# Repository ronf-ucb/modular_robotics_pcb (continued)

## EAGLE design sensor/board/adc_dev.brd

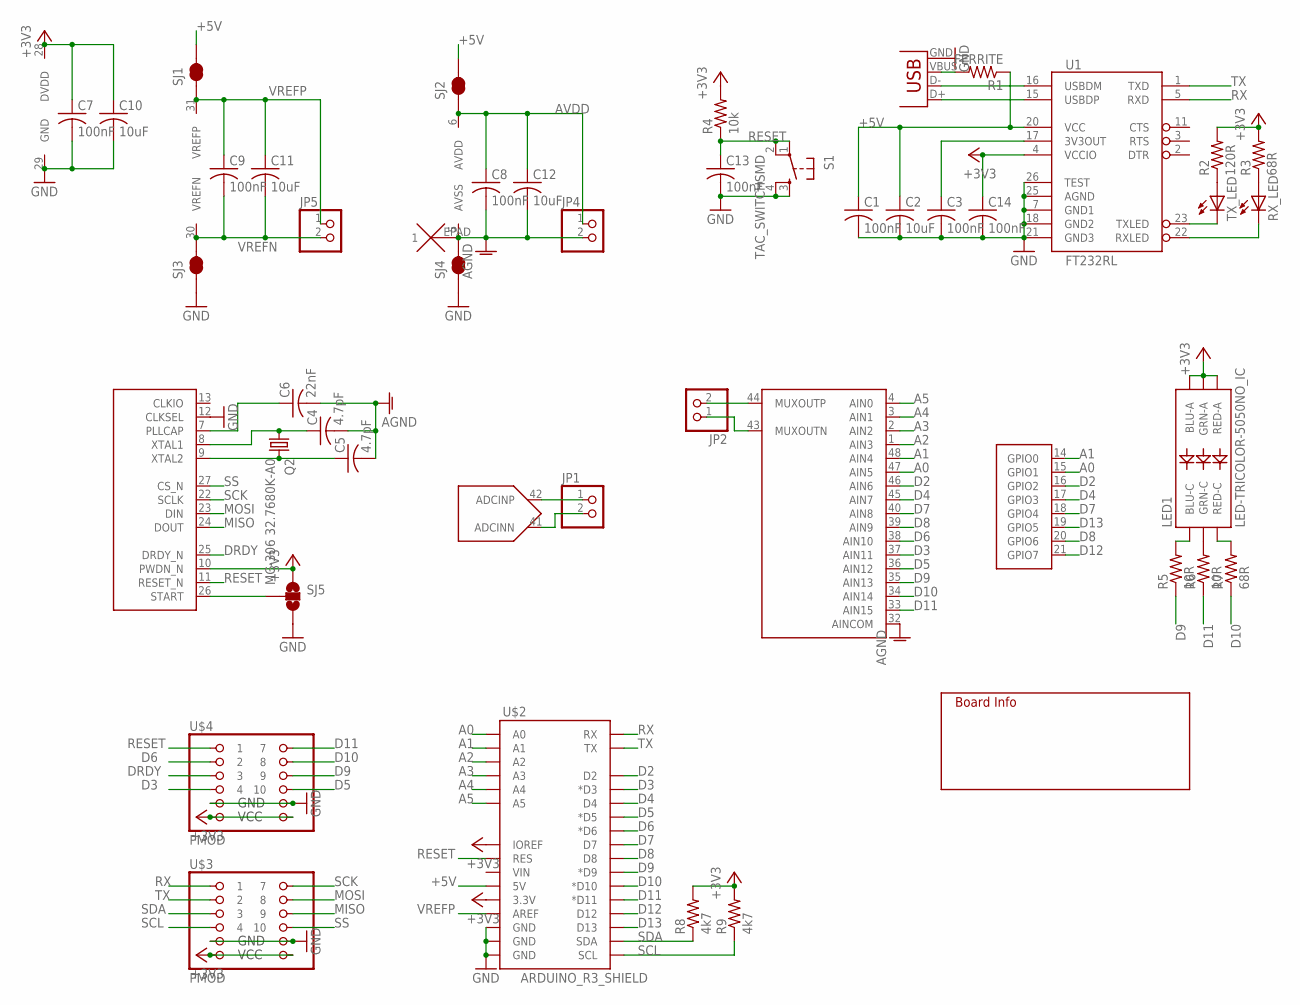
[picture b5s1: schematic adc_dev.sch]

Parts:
C1, C3, C7, C8, C9, C13, C14: 100nF; C0603
C2, C10, C11, C12: 10uF; C0603
C4, C5: 4.7pF; C0603
C6: 22nF; C0603
JP1, JP2, JP4, JP5: PINHD-1X2; 1X02
JP3: USBSMD; USB-MINIB
LED1: LED-TRICOLOR-5050NO_IC; LED-TRICOLOR-5050
Q2: MC-306 32.7680K-A0; MC-306
R1: FERRITE; R0603
R2: 120R; R0603
R3, R7: 68R; R0603
R4: 10k; R0603
R5, R6: 10R; R0603
R8, R9: 4k7; R0603
RX_LED: LEDCHIPLED_0603; CHIPLED_0603
S1: TAC_SWITCHSMD; TACTILE_SWITCH_SMD
SJ1, SJ2, SJ3, SJ4: JUMPER-PAD-2-NC_BY_TRACE; PAD-JUMPER-2-NC_BY_TRACE_YES_SILK
SJ5: JUMPER-PAD-3-NOYES_SILK; PAD-JUMPER-3-NO_YES_SILK
TX_LED: LEDCHIPLED_0603; CHIPLED_0603
U1: FT232RL; SSOP28DB
U$1: ADS1258; QFN-48
U$2: ARDUINO_R3_SHIELD; UNO_R3_SHIELD
U$3, U$4: PMOD; 2X06
U$5: INFO

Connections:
+3V3: C7.1, C10.1, C14.1, LED1.1 (GRN-A), LED1.2 (RED-A), LED1.3 (BLU-A), R2.2, R3.2, R4.2, R8.2, R9.2, SJ5.1, U1.4 (VCCIO), U$1.10 (PWDN_N), U$1.28 (DVDD), U$2.3.3V, U$2.IOREF, U$3.11 (6), U$3.12, U$4.11 (6), U$4.12
+5V: C1.1, C2.1, R1.1, SJ1.2, SJ2.2, U1.20 (VCC), U$2.5V
A0: U$1.15 (GPIO1), U$1.47 (AIN5), U$2.A0
A1: U$1.14 (GPIO0), U$1.48 (AIN4), U$2.A1
A2: U$1.1 (AIN3), U$2.A2
A3: U$1.2 (AIN2), U$2.A3
A4: U$1.3 (AIN1), U$2.A4
A5: U$1.4 (AIN0), U$2.A5
ADCN: JP1.2, U$1.41 (ADCINN)
ADCP: JP1.1, U$1.42 (ADCINP)
AGND: C4.2, C5.2, C6.2, C8.2, C12.2, JP4.2, SJ4.2, U$1.5 (AVSS), U$1.32 (AINCOM), U$1.EPAD (1)
AVDD: C8.1, C12.1, JP4.1, SJ2.1, U$1.6 (AVDD)
D2: U$1.16 (GPIO2), U$1.46 (AIN6), U$2.D2
D3: U$1.37 (AIN11), U$2.D3 (*D3), U$4.7 (4)
D4: U$1.17 (GPIO3), U$1.45 (AIN7), U$2.D4
D5: U$1.36 (AIN12), U$2.D5 (*D5), U$4.8 (10)
D6: U$1.38 (AIN10), U$2.D6 (*D6), U$4.3 (2)
D7: U$1.18 (GPIO4), U$1.40 (AIN8), U$2.D7
D8: U$1.20 (GPIO6), U$1.39 (AIN9), U$2.D8
D9: R5.1, U$1.35 (AIN13), U$2.D9 (*D9), U$4.6 (9)
D10: R7.1, U$1.34 (AIN14), U$2.D10 (*D10), U$4.4 (8)
D11: R6.1, U$1.33 (AIN15), U$2.D11 (*D11), U$4.2 (7)
D12: U$1.21 (GPIO7), U$2.D12
D13: U$1.19 (GPIO5), U$2.D13
DRDY: U$1.25 (DRDY_N), U$4.5 (3)
GND: C1.2, C2.2, C3.2, C7.2, C10.2, C13.2, C14.2, JP3.GND, S1.3, S1.4, SJ3.1, SJ4.1, SJ5.3, U1.7 (GND1), U1.18 (GND2), U1.21 (GND3), U1.25 (AGND), U1.26 (TEST), U$1.12 (CLKSEL), U$1.29 (GND), U$2.GND@0 (GND), U$2.GND@1 (GND), U$2.GND@2 (GND), U$3.9 (5), U$3.10 (11), U$4.9 (5), U$4.10 (11)
MISO: U$1.24 (DOUT), U$3.6 (9)
MOSI: U$1.23 (DIN), U$3.4 (8)
MUXN: JP2.1, U$1.43 (MUXOUTN)
MUXP: JP2.2, U$1.44 (MUXOUTP)
unnamed: JP3.D+, U1.15 (USBDP)
unnamed: JP3.D-, U1.16 (USBDM)
unnamed: R2.1, TX_LED.A
unnamed: R3.1, RX_LED.A
unnamed: C3.1, U1.17 (3V3OUT)
unnamed: SJ5.2, U$1.26 (START)
unnamed: JP3.VBUS, R1.2
unnamed: TX_LED.C, U1.23 (TXLED)
unnamed: RX_LED.C, U1.22 (RXLED)
unnamed: C6.1, U$1.7 (PLLCAP)
unnamed: C4.1, Q2.1, U$1.8 (XTAL1)
unnamed: C5.1, Q2.4 (2), U$1.9 (XTAL2)
unnamed: LED1.4 (BLU-C), R5.2
unnamed: LED1.6 (GRN-C), R6.2
unnamed: LED1.5 (RED-C), R7.2
RESET: C13.1, R4.1, S1.1, S1.2, U$1.11 (RESET_N), U$2.RES, U$4.1
RX: U1.5 (RXD), U$2.RX, U$3.1
SCK: U$1.22 (SCLK), U$3.2 (7)
SCL: R9.1, U$2.SCL, U$3.7 (4)
SDA: R8.1, U$2.SDA, U$3.5 (3)
SS: U$1.27 (CS_N), U$3.8 (10)
TX: U1.1 (TXD), U$2.TX, U$3.3 (2)
VREFN: C9.2, C11.2, JP5.2, SJ3.2, U$1.30 (VREFN)
VREFP: C9.1, C11.1, JP5.1, SJ1.1, U$1.31 (VREFP), U$2.AREF

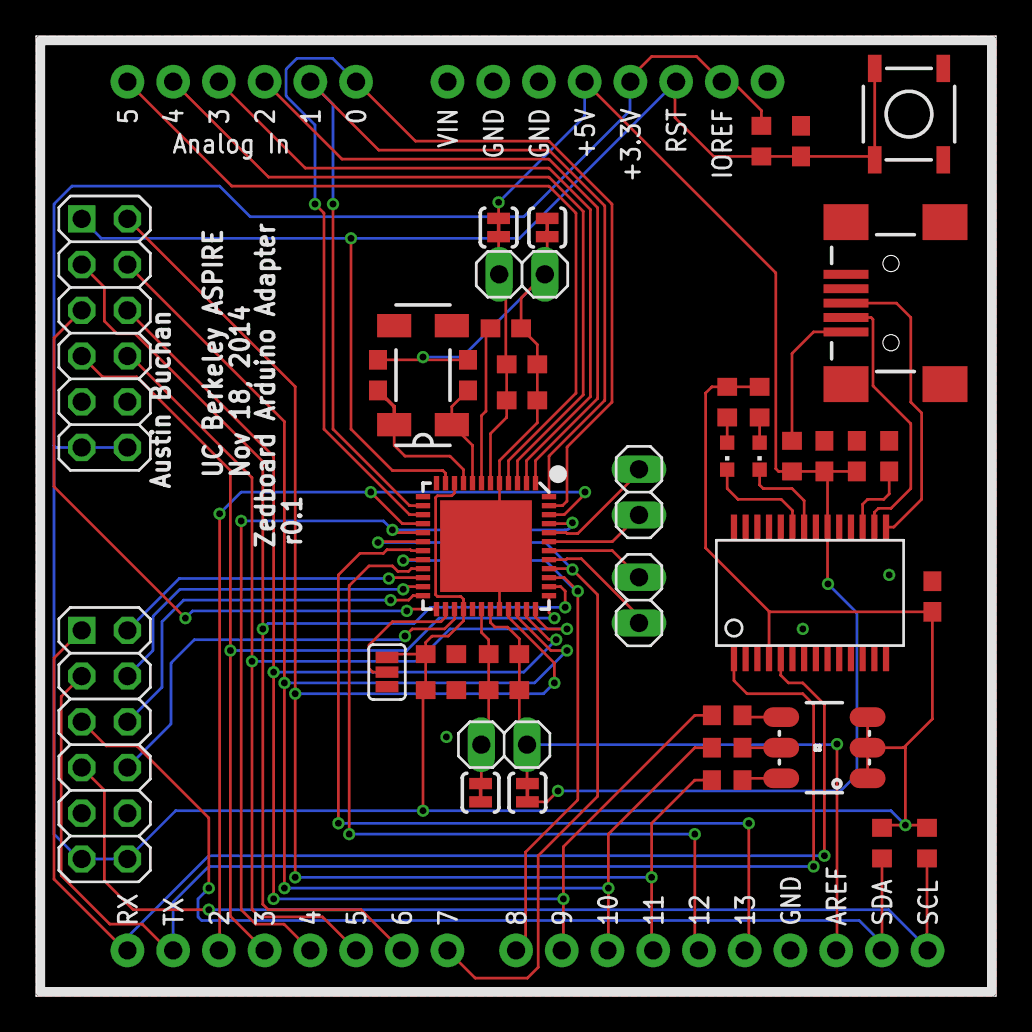
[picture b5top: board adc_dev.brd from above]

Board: 4 copper layers, 53.3 x 53.3 mm, 44 parts (0 on the bottom side), 54 nets.
